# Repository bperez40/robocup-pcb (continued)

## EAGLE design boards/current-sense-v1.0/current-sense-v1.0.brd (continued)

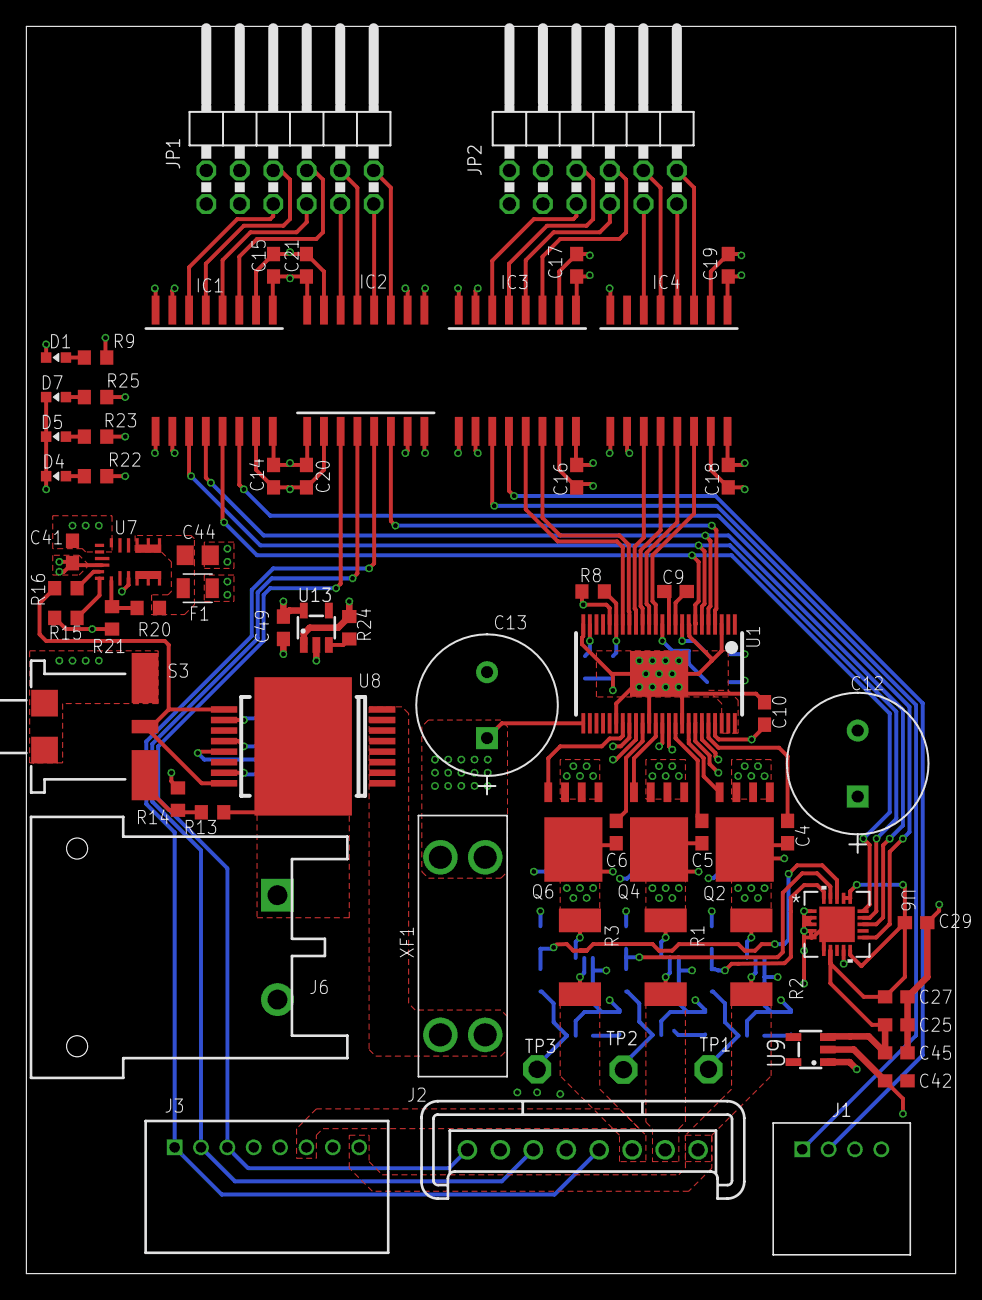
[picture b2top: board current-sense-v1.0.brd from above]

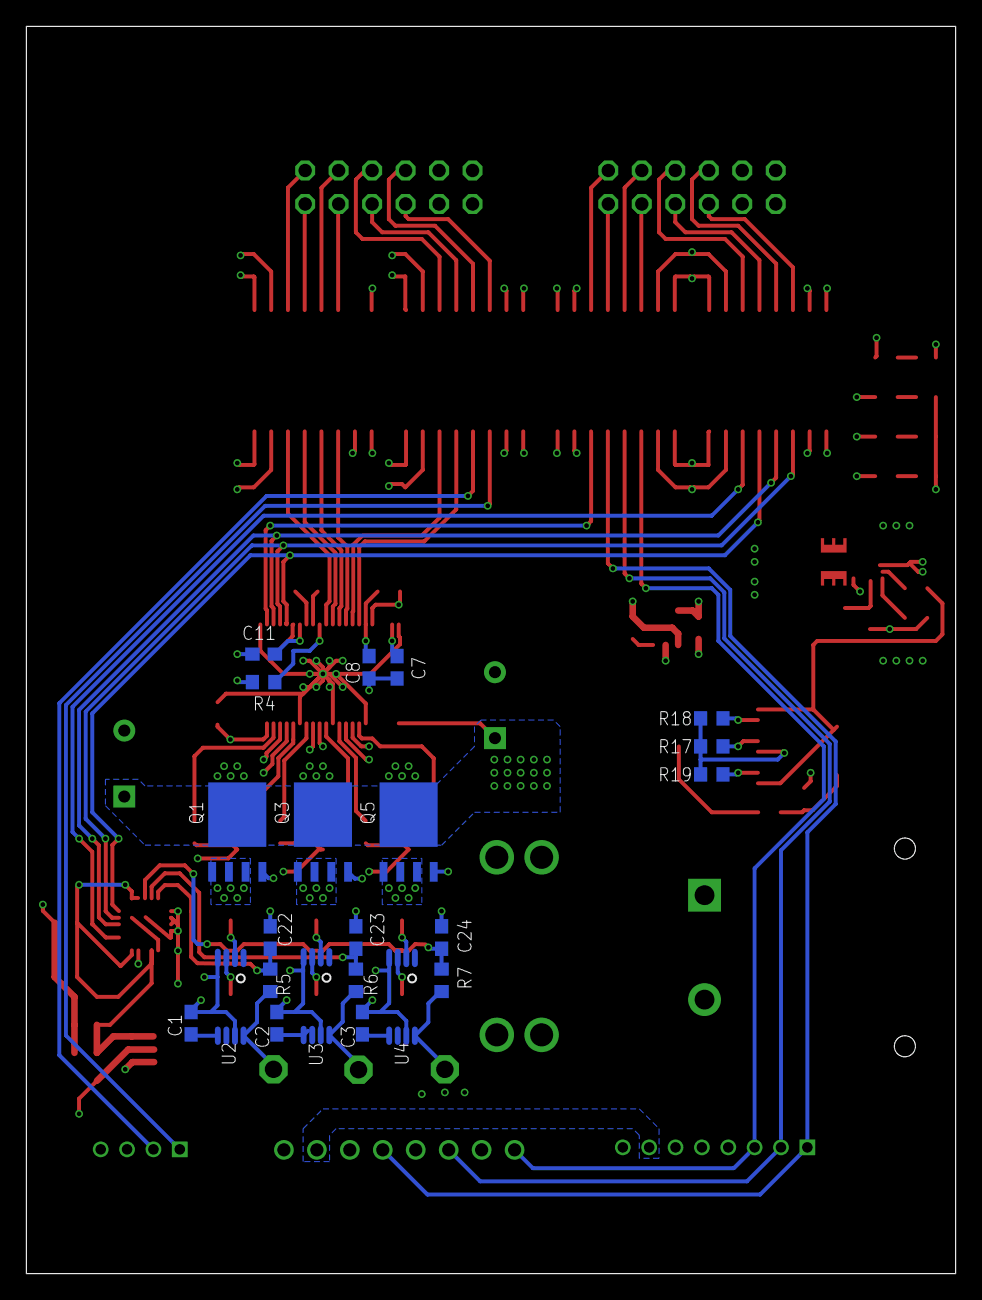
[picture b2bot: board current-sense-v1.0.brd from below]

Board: 4 copper layers, 70.5 x 94.6 mm, 89 parts (22 on the bottom side), 82 nets.

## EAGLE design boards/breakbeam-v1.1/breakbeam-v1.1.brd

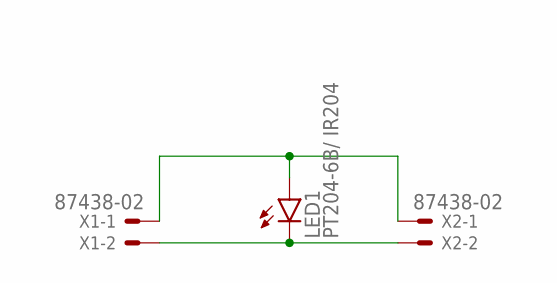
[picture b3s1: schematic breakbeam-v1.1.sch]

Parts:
LED1: PT204-6B/ IR204; LED3MM
X1, X2: 87438-02

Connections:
ANODE: LED1.A, X1.1, X2.1
CATHODE: LED1.K (C), X1.2, X2.2

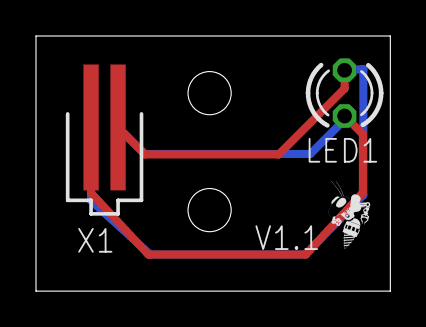
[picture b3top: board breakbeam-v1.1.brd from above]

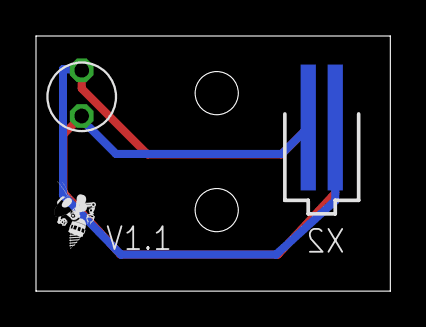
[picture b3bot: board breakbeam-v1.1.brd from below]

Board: 2 copper layers, 19.7 x 14.2 mm, 5 parts (2 on the bottom side), 2 nets.

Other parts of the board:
U$1, U$4: ROBOBUZZ_0.2X

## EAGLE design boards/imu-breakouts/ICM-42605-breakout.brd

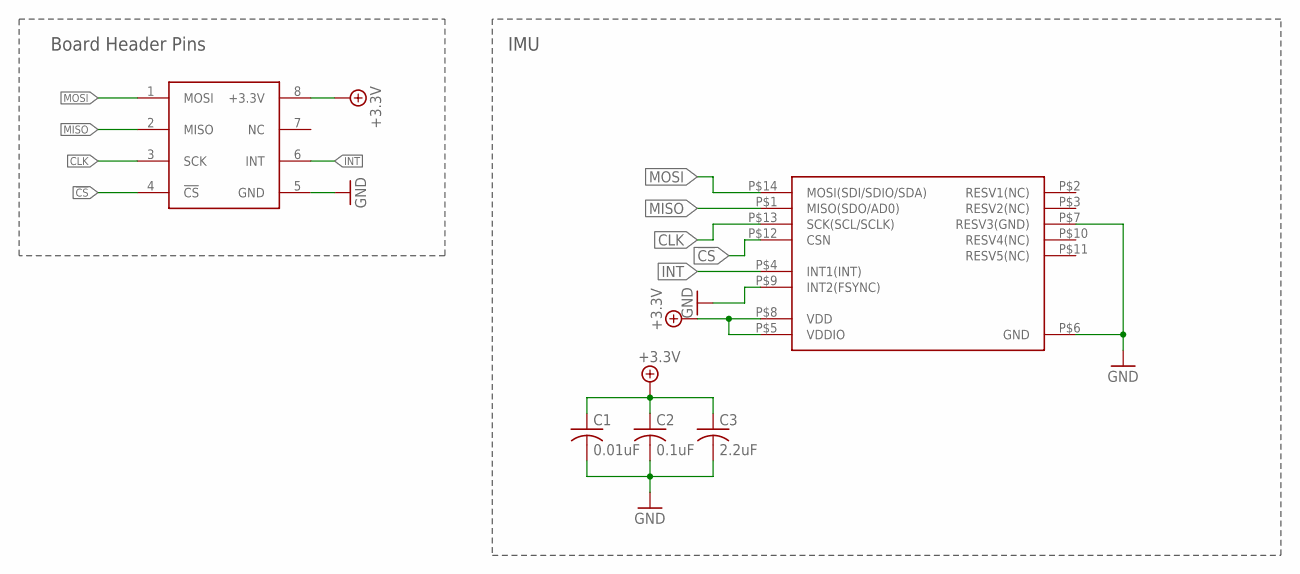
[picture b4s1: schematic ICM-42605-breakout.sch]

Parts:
C1: 0.01uF; C0603
C2: 0.1uF; C0603
C3: 2.2uF; C0603
KIT1: IMUIMU-KIT; IMU-KIT
U3: ICM-42605; ICM-442605-2530091

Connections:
!CS!: KIT1.4 (!CS!), U3.P$12 (CSN)
+3.3V: C1.1, C2.1, C3.1, KIT1.8 (+3.3V), U3.P$5 (VDDIO), U3.P$8 (VDD)
CLK: KIT1.3 (SCK), U3.P$13 (SCK(SCL/SCLK))
GND: C1.2, C2.2, C3.2, KIT1.5 (GND), U3.P$6 (GND), U3.P$7 (RESV3(GND)), U3.P$9 (INT2(FSYNC))
INT: KIT1.6 (INT), U3.P$4 (INT1(INT))
MISO: KIT1.2 (MISO), U3.P$1 (MISO(SDO/AD0))
MOSI: KIT1.1 (MOSI), U3.P$14 (MOSI(SDI/SDIO/SDA))

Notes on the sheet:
IMU
Board Header Pins

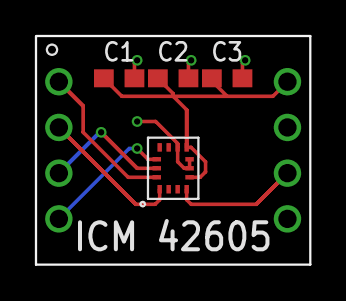
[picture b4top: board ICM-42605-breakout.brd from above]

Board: 2 copper layers, 15.2 x 12.7 mm, 5 parts (0 on the bottom side), 7 nets.

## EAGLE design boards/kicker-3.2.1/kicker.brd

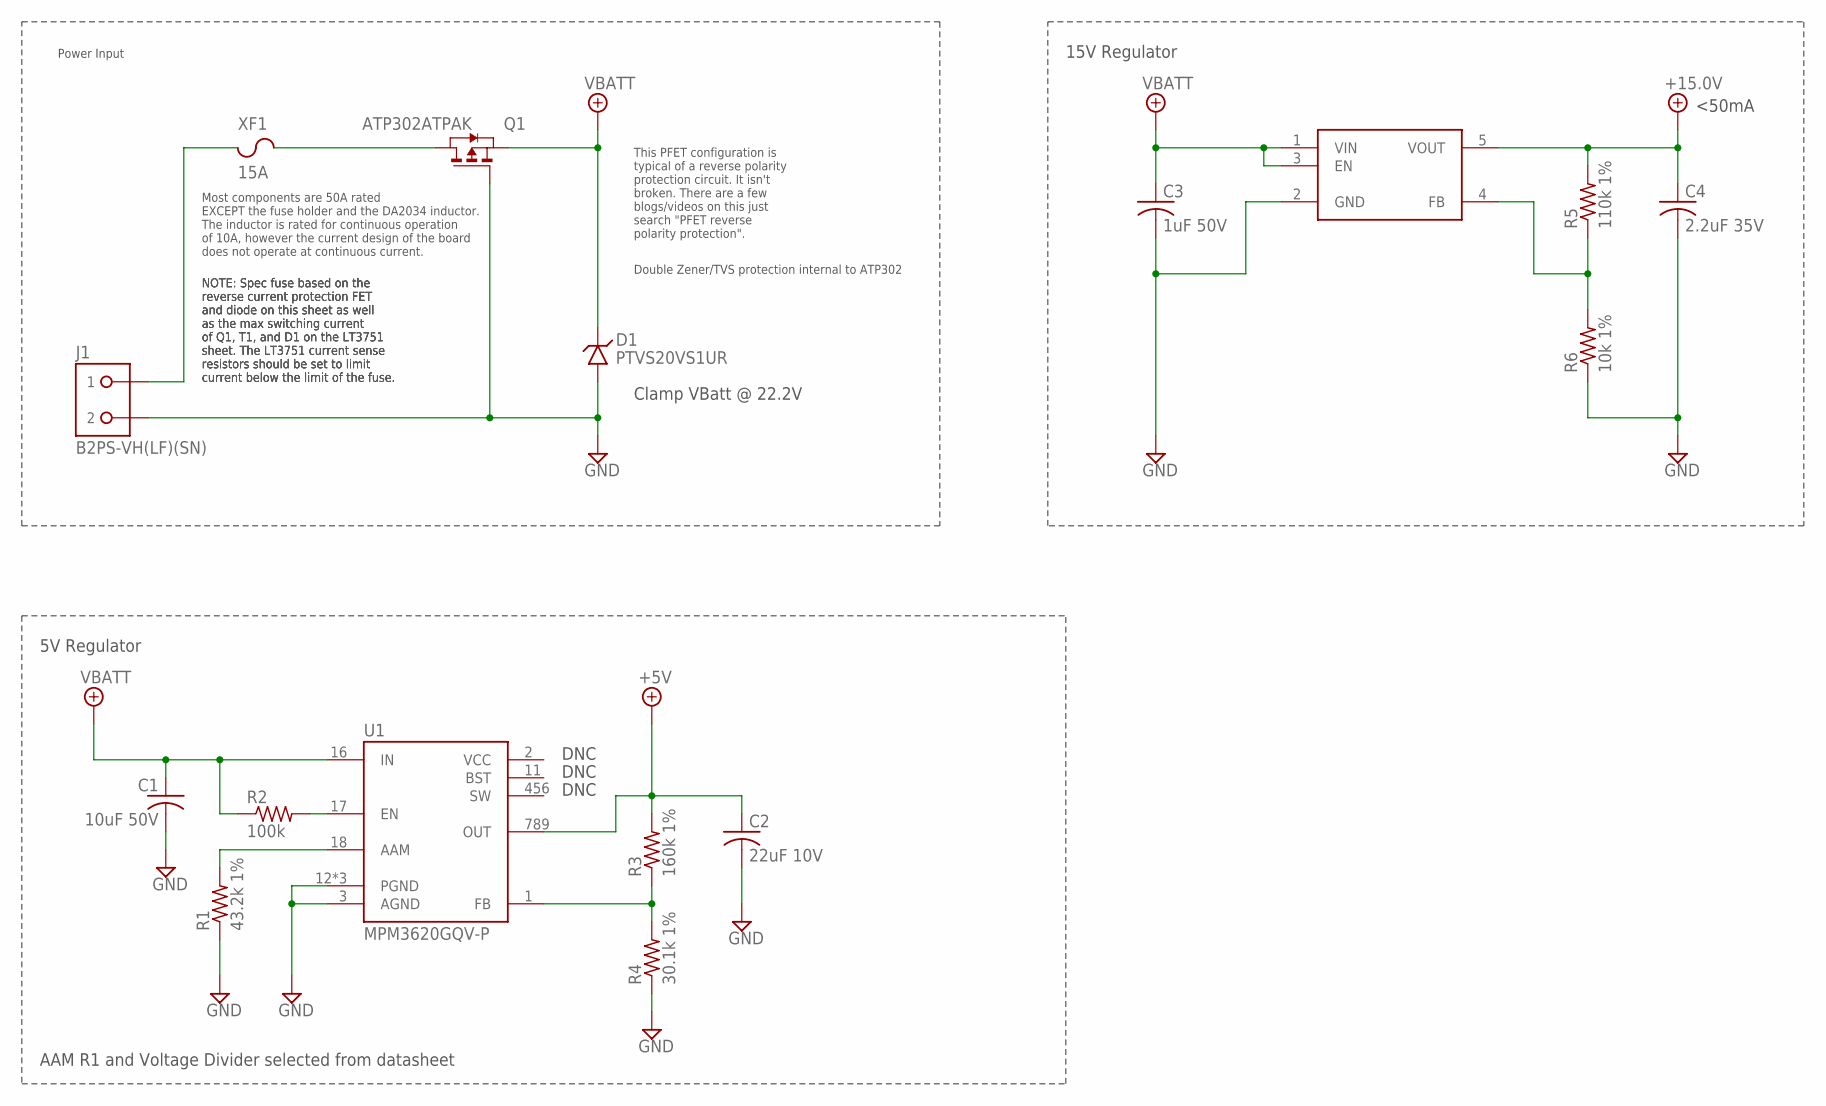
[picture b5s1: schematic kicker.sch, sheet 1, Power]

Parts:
C1: 10uF 50V; C1206
C2: 22uF 10V; C0603
C3: 1uF 50V; C0603
C4: 2.2uF 35V; C0603
D1: PTVS20VS1UR; SOD123-W
J1: B2PS-VH(LF)(SN); B2PS-CENTERED
Q1: ATP302ATPAK; TO460P950X150-3
R1: 43.2k 1%; R0603
R2: 100k; R0603
R3: 160k 1%; R0603
R4: 30.1k 1%; R0603
R5: 110k 1%; R0603
R6: 10k 1%; R0603
U1: MPM3620GQV-P
U2: 15V; SOT95P280X145-5
XF1: 15A; 3557-2

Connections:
+5V: C2.1, R3.2, U1.789 (OUT); also elsewhere on the board
+15.0V: C4.1, R5.2, U2.5 (VOUT); also elsewhere on the board
FB: R3.1, R4.2, U1.1 (FB)
GND: C1.2, C2.2, C3.2, C4.2, D1.A, J1.2, Q1.1 (G), R1.1, R4.1, R6.1, U1.3 (AGND), U1.12 (PGND), U1.13 (PGND), U1.14 (PGND), U2.2 (GND); also elsewhere on the board
unnamed: Q1.3 (D), XF1.3 (2), XF1.4 (2)
unnamed: R5.1, R6.2, U2.4 (FB)
unnamed: J1.1, XF1.1, XF1.2 (1)
REG_AAM: R1.2, U1.18 (AAM)
REG_EN: R2.2, U1.17 (EN)
VBATT: C1.1, C3.1, D1.C, Q1.2 (S), R2.1, U1.16 (IN), U2.1 (VIN), U2.3 (EN); also elsewhere on the board

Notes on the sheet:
Power Input
5V Regulator
NOTE: Spec fuse based on the reverse current protection FET and diode on this sheet as well as the max switching current of Q1, T1, and D1 on the LT3751 sheet. The LT3751 current sense resistors should be set to limit current below the limit of the fuse.
15V Regulator
This PFET configuration is typical of a reverse polarity protection circuit. It isn't broken. There are a few blogs/videos on this just search "PFET reverse polarity protection".
DNC
Clamp VBatt @ 22.2V
<50mA
AAM R1 and Voltage Divider selected from datasheet
Most components are 50A rated EXCEPT the fuse holder and the DA2034 inductor. The inductor is rated for continuous operation of 10A, however the current design of the board does not operate at continuous current.
Double Zener/TVS protection internal to ATP302

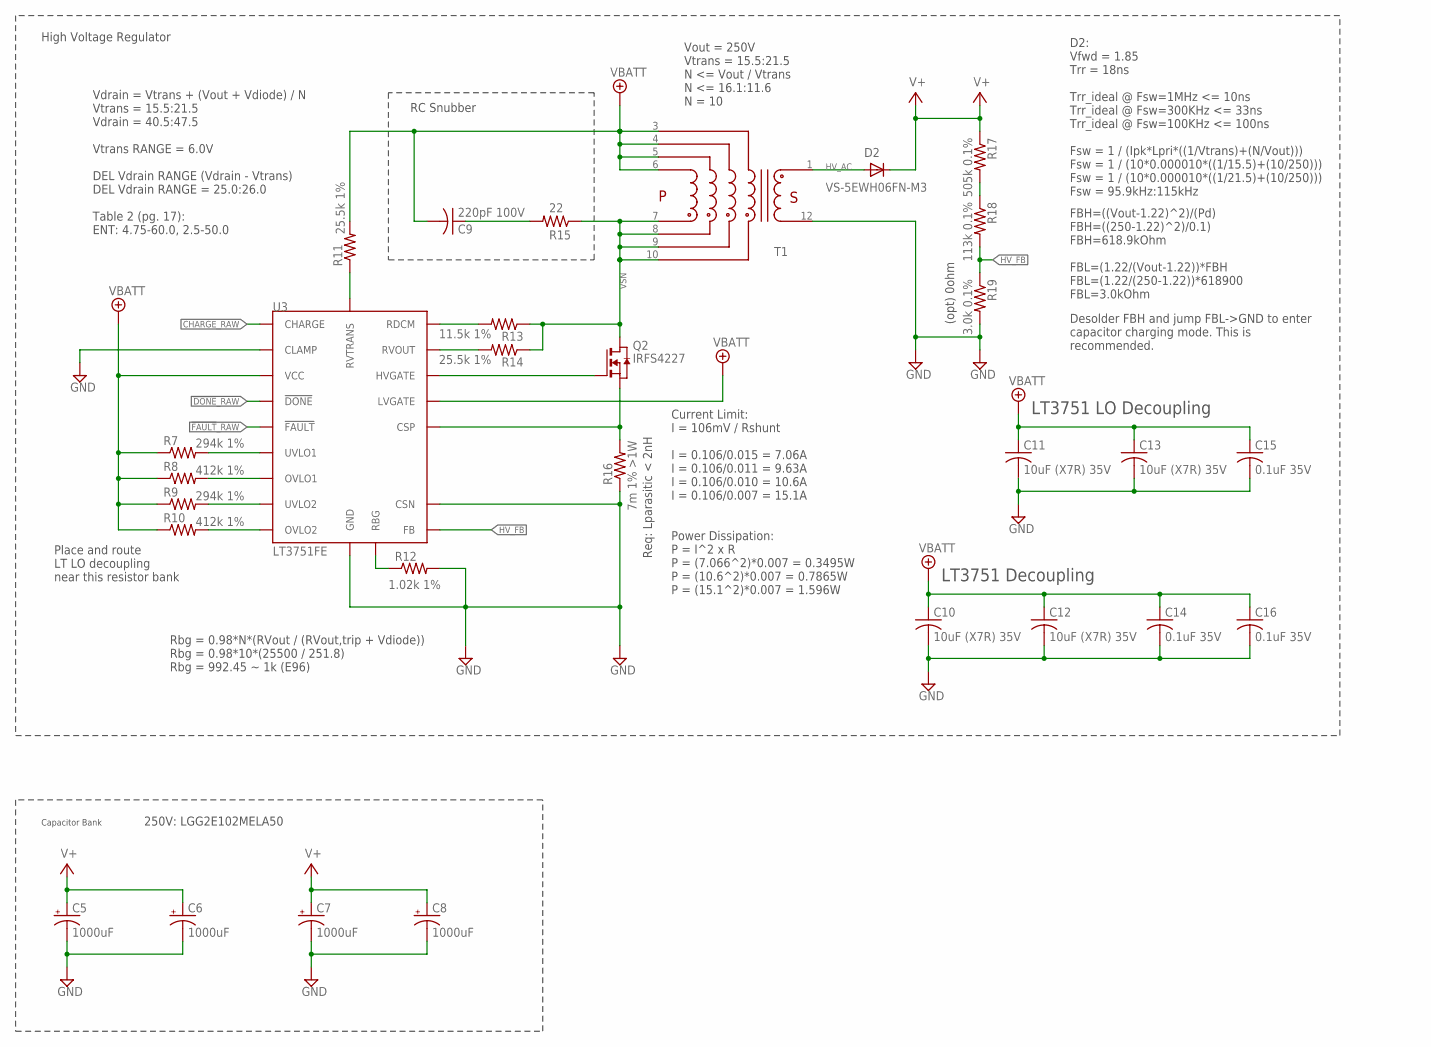
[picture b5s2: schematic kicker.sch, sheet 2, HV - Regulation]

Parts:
C5, C6, C7, C8: 1000uF; EB25D
C9: 220pF 100V; C0805
C10, C11, C12, C13: 10uF (X7R) 35V; C1210
C14, C15, C16: 0.1uF 35V; C0603
D2: VS-5EWH06FN-M3; TO460P990X239-3
Q2: IRFS4227; D2PAK
R7, R9: 294k 1%; R0603
R8, R10: 412k 1%; R0603
R11: 25.5k 1%; R0603
R12: 1.02k 1%; R0805
R13: 11.5k 1%; R0805
R14: 25.5k 1%; R0805
R15: 22; R0805
R16: 7m 1% >1W; R2512
R17: 505k 0.1%; R0603
R18: 113k 0.1%; R0603
R19: 3.0k 0.1%; R0603
T1: DA203X-ALDA2034; DA2034
U3: LT3751FE; TSSOP-20_EP

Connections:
!DONE!_RAW: U3.7 (!DONE); also elsewhere on the board
!FAULT!_RAW: U3.6 (!FAULT); also elsewhere on the board
CHARGE_RAW: U3.8 (CHARGE); also elsewhere on the board
CSP: Q2.3 (S), R16.2, U3.12 (CSP)
GND: C5.-, C6.-, C7.-, C8.-, C10.2, C11.2, C12.2, C13.2, C14.2, C15.2, C16.2, R12.2, R16.1, R19.2, T1.12, U3.9 (CLAMP), U3.11 (CSN), U3.PAD (GND); also elsewhere on the board
HVGATE: Q2.1 (G), U3.15 (HVGATE)
HV_AC: D2.2 (A), T1.1
HV_FB: R18.2, R19.1, U3.10 (FB)
unnamed: R12.1, U3.16 (RBG)
unnamed: R17.2, R18.1
unnamed: C9.1, R15.2
unnamed: R11.1, U3.1 (RVTRANS)
OVLO1: R8.2, U3.3 (OVLO1)
OVLO2: R10.2, U3.5 (OVLO2)
RDCM: R13.2, U3.20 (RDCM)
RVOUT: R14.2, U3.18 (RVOUT)
UVLO1: R7.2, U3.2 (UVLO1)
UVLO2: R9.2, U3.4 (UVLO2)
V+: C5.+, C6.+, C7.+, C8.+, D2.3 (C), R17.1; also elsewhere on the board
VBATT: C9.2, C10.1, C11.1, C12.1, C13.1, C14.1, C15.1, C16.1, R7.1, R8.1, R9.1, R10.1, R11.2, T1.3, T1.4, T1.5, T1.6, U3.13 (VCC), U3.14 (LVGATE); also elsewhere on the board
VSN: Q2.2 (D), R13.1, R14.1, R15.1, T1.7, T1.8, T1.9, T1.10

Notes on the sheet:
Capacitor Bank
High Voltage Regulator
250V: LGG2E102MELA50
RC Snubber
LT3751 LO Decoupling
LT3751 Decoupling
Place and route LT LO decoupling near this resistor bank
Desolder FBH and jump FBL->GND to enter capacitor charging mode. This is recommended.
(opt) 0ohm
Current Limit: I = 106mV / Rshunt I = 0.106/0.015 = 7.06A I = 0.106/0.011 = 9.63A I = 0.106/0.010 = 10.6A I = 0.106/0.007 = 15.1A Power Dissipation: P = I^2 x R P = (7.066^2)*0.007 = 0.3495W P = (10.6^2)*0.007 = 0.7865W P = (15.1^2)*0.007 = 1.596W
Vdrain = Vtrans + (Vout + Vdiode) / N Vtrans = 15.5:21.5 Vdrain = 40.5:47.5 Vtrans RANGE = 6.0V DEL Vdrain RANGE (Vdrain - Vtrans) DEL Vdrain RANGE = 25.0:26.0 Table 2 (pg. 17): ENT: 4.75-60.0, 2.5-50.0
Req: Lparasitic < 2nH
Rbg = 0.98*N*(RVout / (RVout,trip + Vdiode)) Rbg = 0.98*10*(25500 / 251.8) Rbg = 992.45 ~ 1k (E96)
Vout = 250V Vtrans = 15.5:21.5 N <= Vout / Vtrans N <= 16.1:11.6 N = 10
D2: Vfwd = 1.85 Trr = 18ns Trr_ideal @ Fsw=1MHz <= 10ns Trr_ideal @ Fsw=300KHz <= 33ns Trr_ideal @ Fsw=100KHz <= 100ns Fsw = 1 / (Ipk*Lpri*((1/Vtrans)+(N/Vout))) Fsw = 1 / (10*0.000010*((1/15.5)+(10/250))) Fsw = 1 / (10*0.000010*((1/21.5)+(10/250))) Fsw = 95.9kHz:115kHz
FBH=((Vout-1.22)^2)/(Pd) FBH=((250-1.22)^2)/0.1) FBH=618.9kOhm FBL=(1.22/(Vout-1.22))*FBH FBL=(1.22/(250-1.22))*618900 FBL=3.0kOhm

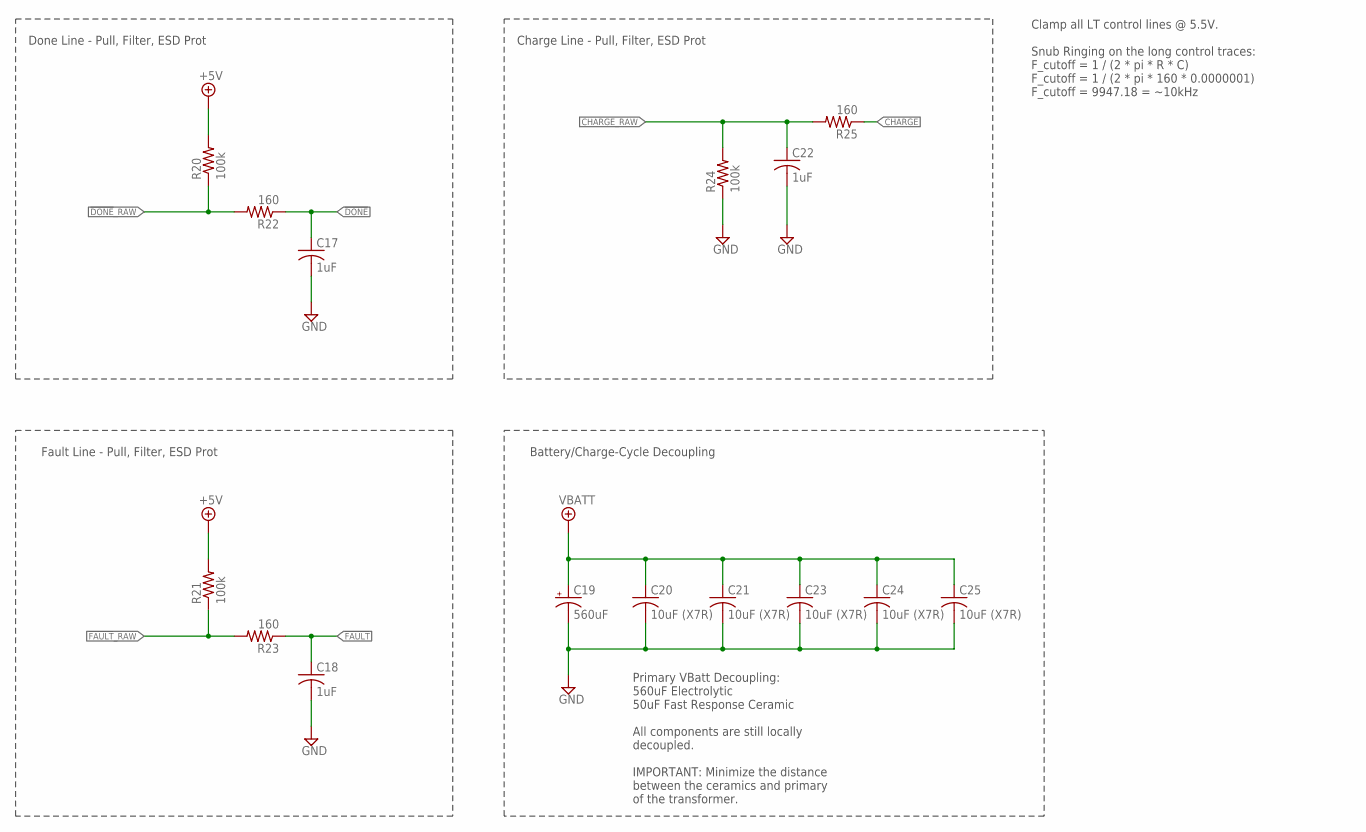
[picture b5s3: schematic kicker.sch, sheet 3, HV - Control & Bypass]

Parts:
C17, C18, C22: 1uF; C0603
C19: 560uF; E7,5-18
C20, C21, C23, C24, C25: 10uF (X7R); C1210
R20, R21, R24: 100k; R0603
R22, R23, R25: 160; R0603

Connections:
!DONE!: C17.1, R22.1; also elsewhere on the board
!DONE!_RAW: R20.1, R22.2; also elsewhere on the board
!FAULT!: C18.1, R23.1; also elsewhere on the board
!FAULT!_RAW: R21.1, R23.2; also elsewhere on the board
+5V: R20.2, R21.2; also elsewhere on the board
CHARGE: R25.1; also elsewhere on the board
CHARGE_RAW: C22.1, R24.2, R25.2; also elsewhere on the board
GND: C17.2, C18.2, C19.-, C20.2, C21.2, C22.2, C23.2, C24.2, C25.2, R24.1; also elsewhere on the board
VBATT: C19.+, C20.1, C21.1, C23.1, C24.1, C25.1; also elsewhere on the board

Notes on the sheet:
Done Line - Pull, Filter, ESD Prot
Fault Line - Pull, Filter, ESD Prot
Charge Line - Pull, Filter, ESD Prot
Battery/Charge-Cycle Decoupling
Clamp all LT control lines @ 5.5V. Snub Ringing on the long control traces: F_cutoff = 1 / (2 * pi * R * C) F_cutoff = 1 / (2 * pi * 160 * 0.0000001) F_cutoff = 9947.18 = ~10kHz
Primary VBatt Decoupling: 560uF Electrolytic 50uF Fast Response Ceramic All components are still locally decoupled. IMPORTANT: Minimize the distance between the ceramics and primary of the transformer.

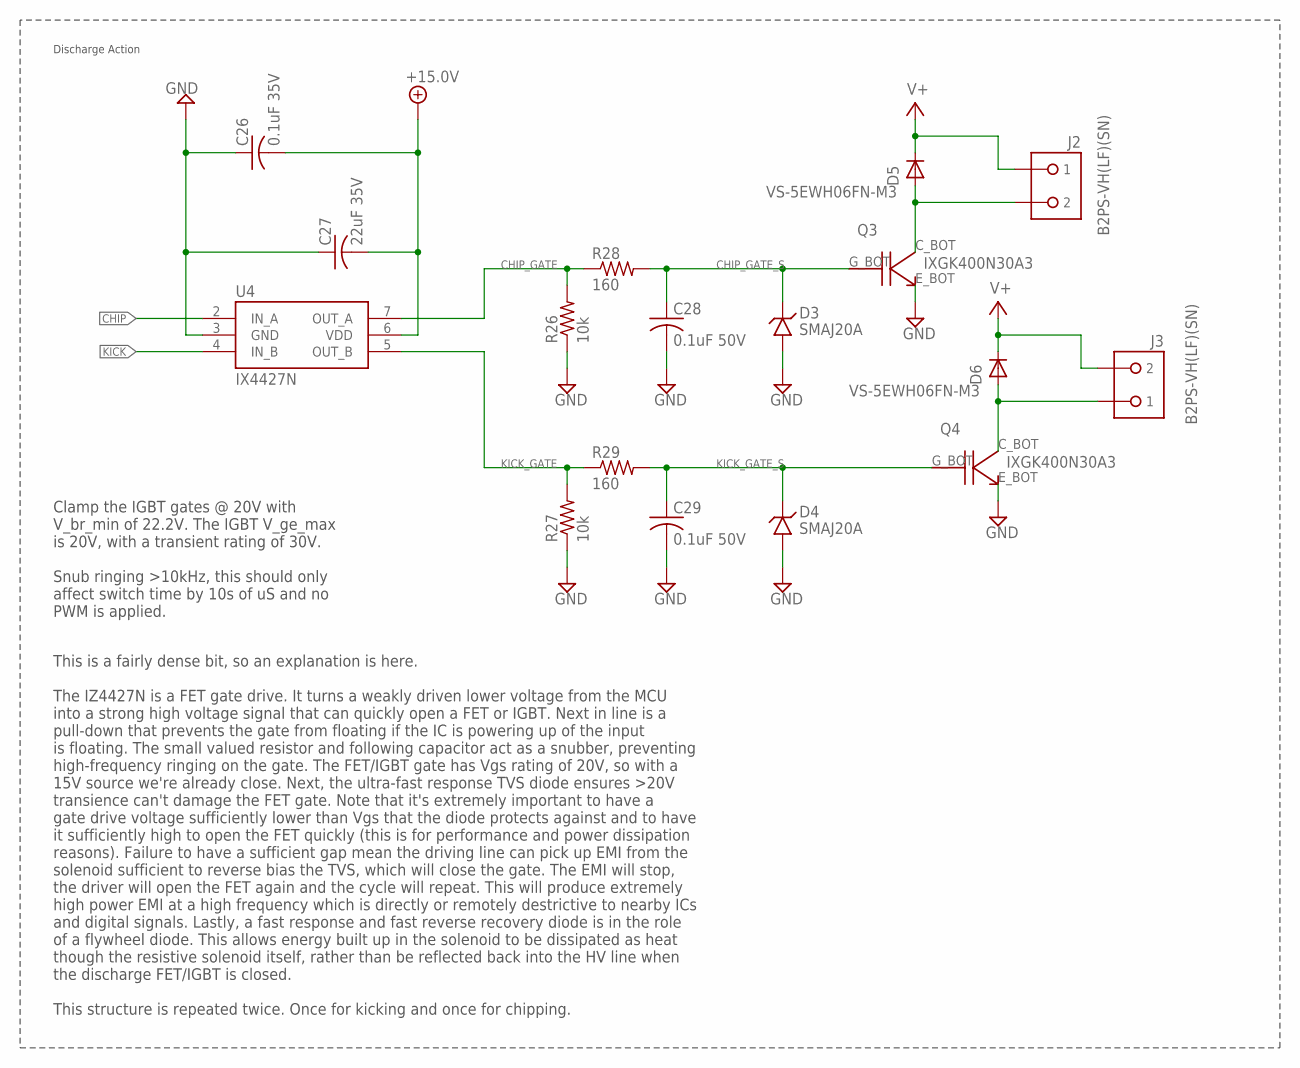
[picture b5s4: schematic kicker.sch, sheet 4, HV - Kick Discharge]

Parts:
C26: 0.1uF 35V; C0603
C27: 22uF 35V; C0603
C28, C29: 0.1uF 50V; C0603
D3, D4: SMAJ20A; RESM5226X262
D5, D6: VS-5EWH06FN-M3; TO460P990X239-3
J2, J3: B2PS-VH(LF)(SN); B2PS-CENTERED
Q3, Q4: IXGK400N30A3; TO264
R26, R27: 10k; R0603
R28, R29: 160; R1206
U4: IX4427N; SOIC-8

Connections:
+15.0V: C26.2, C27.2, U4.6 (VDD); also elsewhere on the board
CHIP: U4.2 (IN_A); also elsewhere on the board
CHIPPER: D5.2 (A), J2.2, Q3.C_BOT (C)
CHIP_GATE: R26.2, R28.1, U4.7 (OUT_A)
CHIP_GATE_S: C28.1, D3.2 (C), Q3.G_BOT (G), R28.2
GND: C26.1, C27.1, C28.2, C29.2, D3.1 (A), D4.1 (A), Q3.E_BOT (E), Q4.E_BOT (E), R26.1, R27.1, U4.3 (GND); also elsewhere on the board
KICK: U4.4 (IN_B); also elsewhere on the board
KICKER: D6.2 (A), J3.1, Q4.C_BOT (C)
KICK_GATE: R27.2, R29.1, U4.5 (OUT_B)
KICK_GATE_S: C29.1, D4.2 (C), Q4.G_BOT (G), R29.2
V+: D5.3 (C), D6.3 (C), J2.1, J3.2; also elsewhere on the board

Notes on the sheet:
Discharge Action
Clamp the IGBT gates @ 20V with V_br_min of 22.2V. The IGBT V_ge_max is 20V, with a transient rating of 30V. Snub ringing >10kHz, this should only affect switch time by 10s of uS and no PWM is applied.
This is a fairly dense bit, so an explanation is here. The IZ4427N is a FET gate drive. It turns a weakly driven lower voltage from the MCU into a strong high voltage signal that can quickly open a FET or IGBT. Next in line is a pull-down that prevents the gate from floating if the IC is powering u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

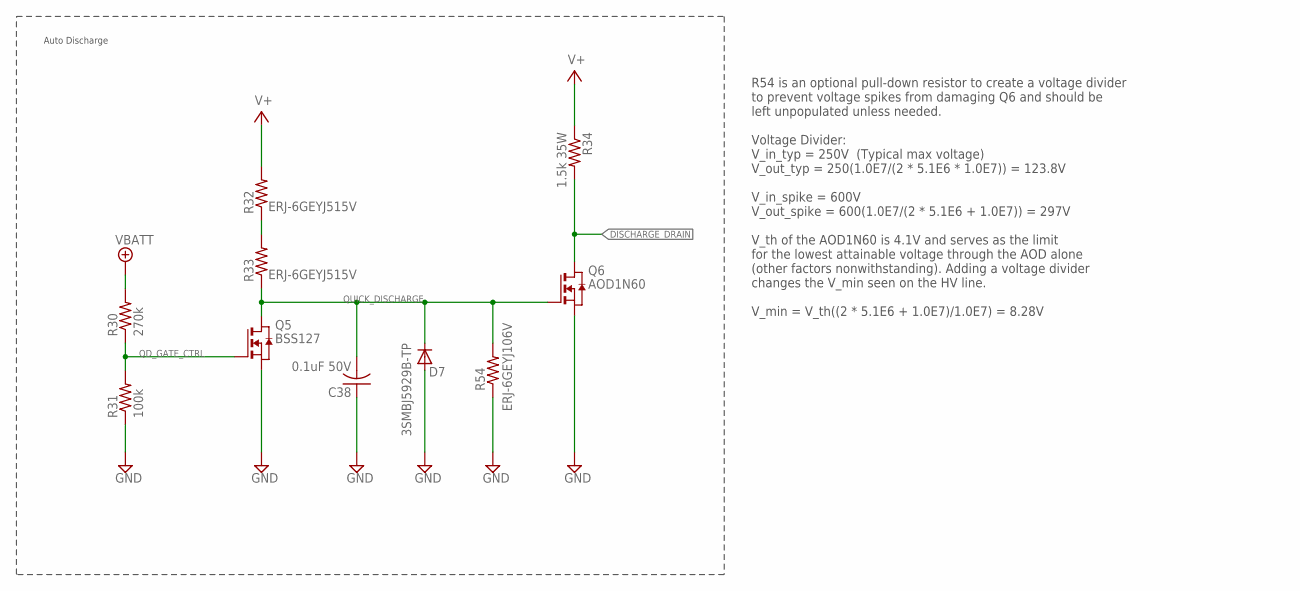
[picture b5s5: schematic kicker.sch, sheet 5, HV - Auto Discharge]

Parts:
C38: 0.1uF 50V; C0603
D7: 3SMBJ5929B-TP; DO214AA
Q5: BSS127; SOT-23-3
Q6: AOD1N60; DPAK
R30: 270k; R0603
R31: 100k; R0603
R32: ERJ-6GEYJ515V; R0603
R33: ERJ-6GEYJ515V; R0805
R34: 1.5k 35W; TO508P1539X450-3
R54: ERJ-6GEYJ106V; R0603

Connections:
DISCHARGE_DRAIN: Q6.FIN (D), R34.2 (PIN2); also elsewhere on the board
GND: C38.1, D7.A, Q5.2 (S), Q6.3 (S), R31.1, R54.1; also elsewhere on the board
QD_GATE_CTRL: Q5.1 (G), R30.1, R31.2
QD_PU_BR: R32.1, R33.2
QUICK_DISCHARGE: C38.2, D7.C, Q5.3 (D), Q6.1 (G), R33.1, R54.2
V+: R32.2, R34.1 (PIN1); also elsewhere on the board
VBATT: R30.2; also elsewhere on the board

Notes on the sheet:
Auto Discharge
R54 is an optional pull-down resistor to create a voltage divider to prevent voltage spikes from damaging Q6 and should be left unpopulated unless needed. Voltage Divider: V_in_typ = 250V (Typical max voltage) V_out_typ = 250(1.0E7/(2 * 5.1E6 * 1.0E7)) = 123.8V V_in_spike = 600V V_out_spike = 600(1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

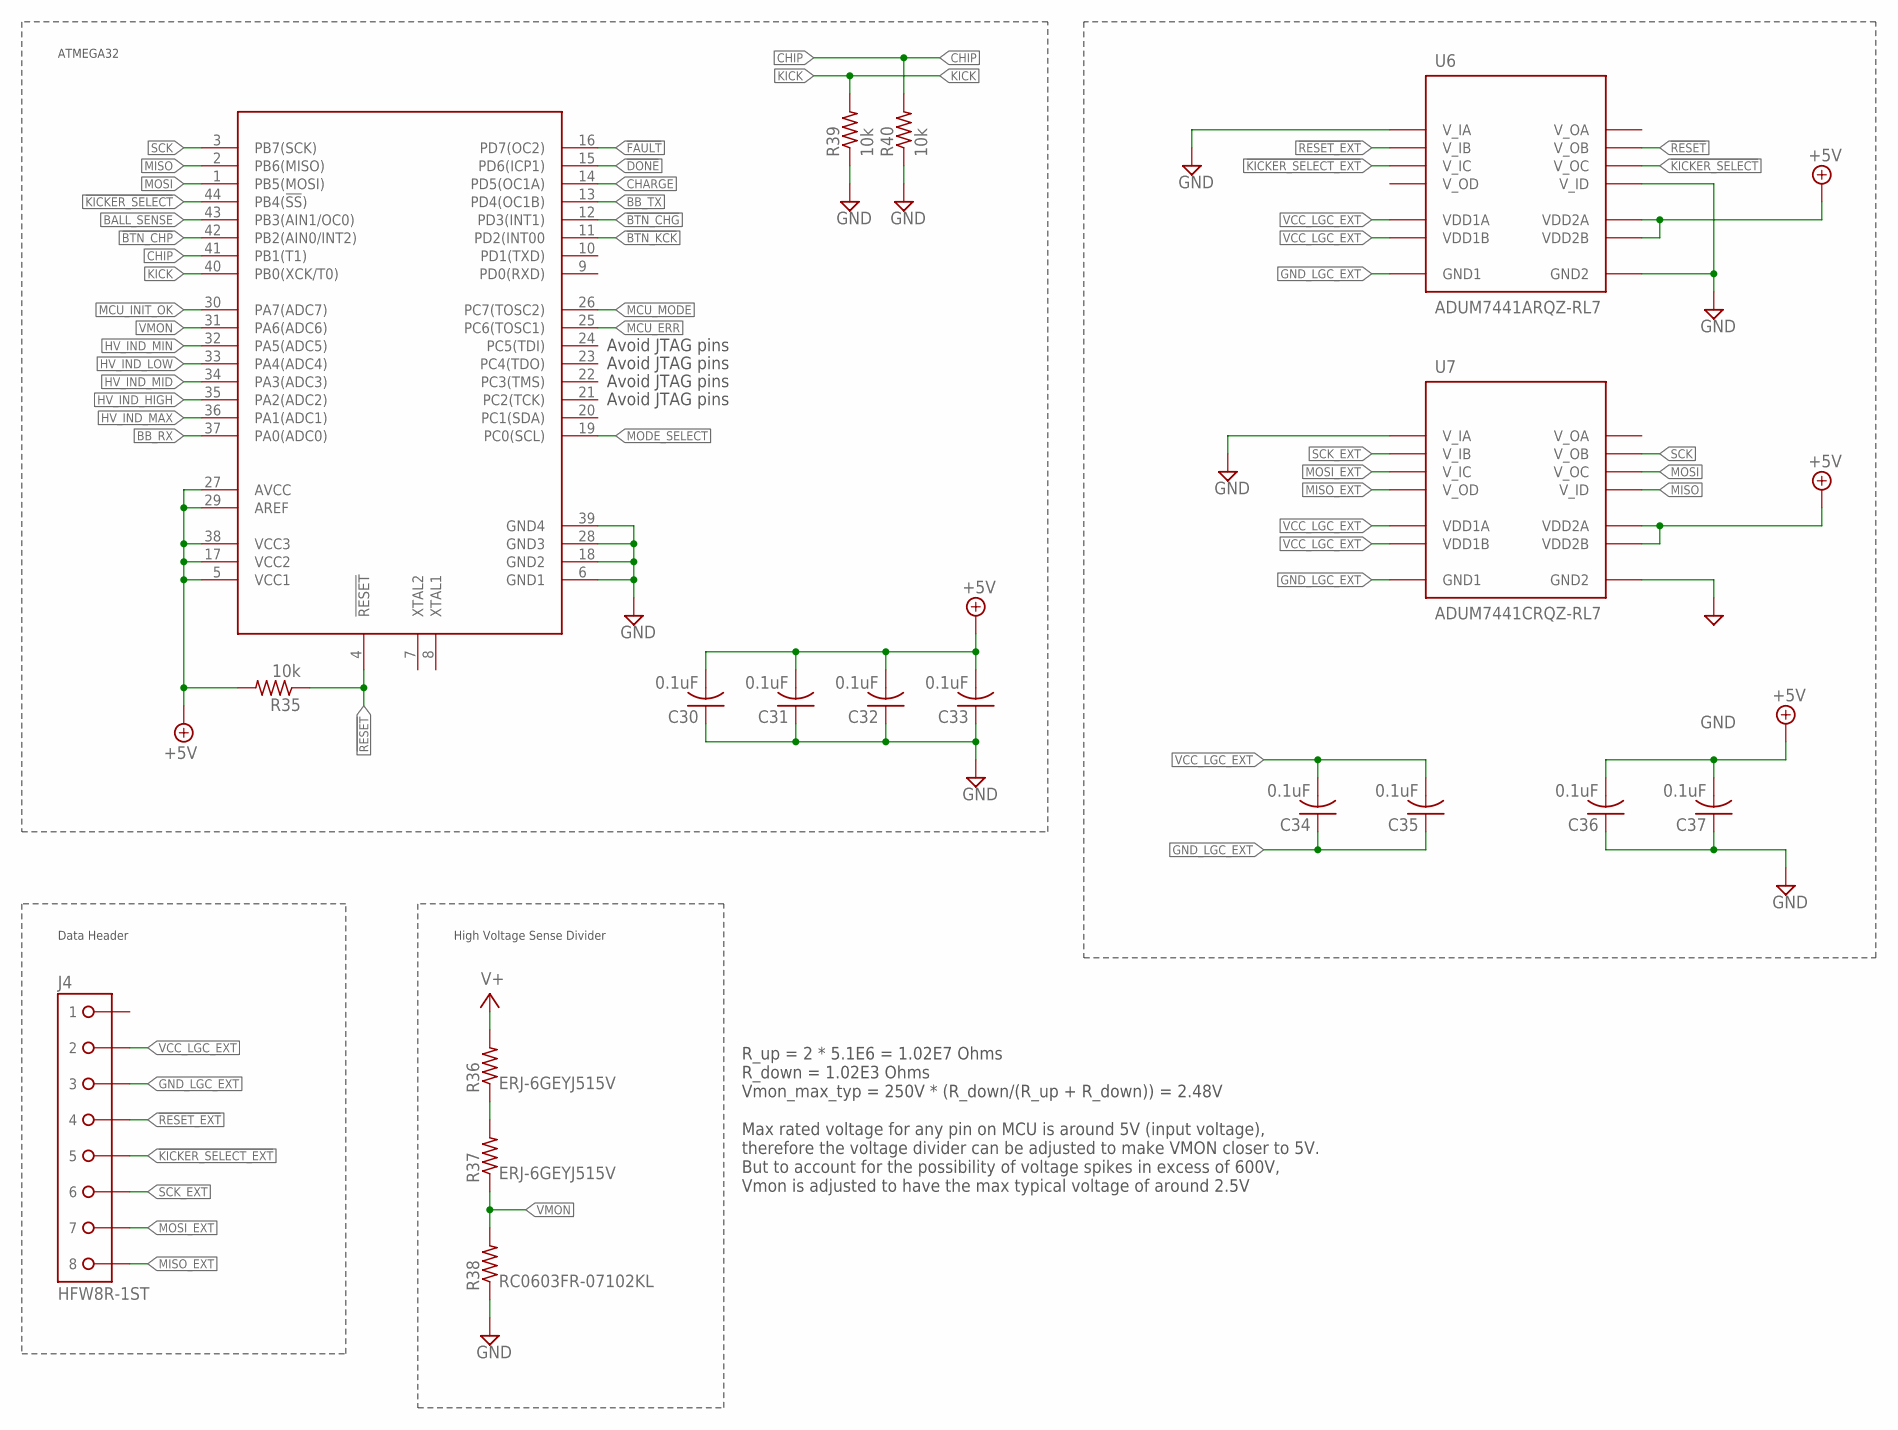
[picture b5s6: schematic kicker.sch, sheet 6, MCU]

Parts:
C30, C31, C32, C33, C34, C35, C36, C37: 0.1uF; C0603
J4: HFW8R-1ST
R35, R39, R40: 10k; R0603
R36, R37: ERJ-6GEYJ515V; R0603
R38: RC0603FR-07102KL; R0603
U5: AT32ATQFP44; QFP80P1200X1200X120-44
U6: ADUM7441ARQZ-RL7; SOP63P574X165-16
U7: ADUM7441CRQZ-RL7; SOP63P574X165-16

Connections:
!BTN_CHG: U5.12 (PD3(INT1)); also elsewhere on the board
!BTN_CHP: U5.42 (PB2(AIN0/INT2)); also elsewhere on the board
!BTN_KCK: U5.11 (PD2(INT00); also elsewhere on the board
!DONE!: U5.15 (PD6(ICP1)); also elsewhere on the board
!FAULT!: U5.16 (PD7(OC2)); also elsewhere on the board
!KICKER_SELECT: U5.44 (PB4(!SS!)), U6.12 (V_OC)
!KICKER_SELECT_EXT: J4.5, U6.5 (V_IC)
!RESET: R35.1, U5.4 (!RESET!), U6.13 (V_OB)
!RESET_EXT: J4.4, U6.4 (V_IB)
+5V: C30.2, C31.2, C32.2, C33.2, C36.2, C37.2, R35.2, U5.5 (VCC1), U5.17 (VCC2), U5.27 (AVCC), U5.29 (AREF), U5.38 (VCC3), U6.10 (VDD2B), U6.16 (VDD2A), U7.10 (VDD2B), U7.16 (VDD2A); also elsewhere on the board
BALL_SENSE: U5.43 (PB3(AIN1/OC0)); also elsewhere on the board
BB_RX: U5.37 (PA0(ADC0)); also elsewhere on the board
BB_TX: U5.13 (PD4(OC1B)); also elsewhere on the board
CHARGE: U5.14 (PD5(OC1A)); also elsewhere on the board
CHIP: R40.2, U5.41 (PB1(T1)); also elsewhere on the board
GND: C30.1, C31.1, C32.1, C33.1, C36.1, C37.1, R38.1, R39.1, R40.1, U5.6 (GND1), U5.18 (GND2), U5.28 (GND3), U5.39 (GND4), U6.3 (V_IA), U6.9 (GND2), U6.11 (V_ID), U6.15 (GND2), U7.3 (V_IA), U7.9 (GND2), U7.15 (GND2); also elsewhere on the board
GND_LGC_EXT: C34.1, C35.1, J4.3, U6.2 (GND1), U6.8 (GND1), U7.2 (GND1), U7.8 (GND1)
HV_IND_HIGH: U5.35 (PA2(ADC2)); also elsewhere on the board
HV_IND_LOW: U5.33 (PA4(ADC4)); also elsewhere on the board
HV_IND_MAX: U5.36 (PA1(ADC1)); also elsewhere on the board
HV_IND_MID: U5.34 (PA3(ADC3)); also elsewhere on the board
HV_IND_MIN: U5.32 (PA5(ADC5)); also elsewhere on the board
HV_SENSE_DIV_BR: R36.1, R37.2
KICK: R39.2, U5.40 (PB0(XCK/T0)); also elsewhere on the board
MCU_ERR: U5.25 (PC6(TOSC1)); also elsewhere on the board
MCU_INIT_OK: U5.30 (PA7(ADC7)); also elsewhere on the board
MCU_MODE: U5.26 (PC7(TOSC2)); also elsewhere on the board
MISO: U5.2 (PB6(MISO)), U7.11 (V_ID)
MISO_EXT: J4.8, U7.6 (V_OD)
MODE_SELECT: U5.19 (PC0(SCL)); also elsewhere on the board
MOSI: U5.1 (PB5(MOSI)), U7.12 (V_OC)
MOSI_EXT: J4.7, U7.5 (V_IC)
SCK: U5.3 (PB7(SCK)), U7.13 (V_OB)
SCK_EXT: J4.6, U7.4 (V_IB)
V+: R36.2; also elsewhere on the board
VCC_LGC_EXT: C34.2, C35.2, J4.2, U6.1 (VDD1A), U6.7 (VDD1B), U7.1 (VDD1A), U7.7 (VDD1B)
VMON: R37.1, R38.2, U5.31 (PA6(ADC6))

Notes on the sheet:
ATMEGA32
Data Header
High Voltage Sense Divider
Avoid JTAG pins
R_up = 2 * 5.1E6 = 1.02E7 Ohms R_down = 1.02E3 Ohms Vmon_max_typ = 250V * (R_down/(R_up + R_down)) = 2.48V Max rated voltage for any pin on MCU is around 5V (input voltage), therefore the voltage divider can be adjusted to make VMON closer to 5V. But to account for the possibility of voltage spikes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

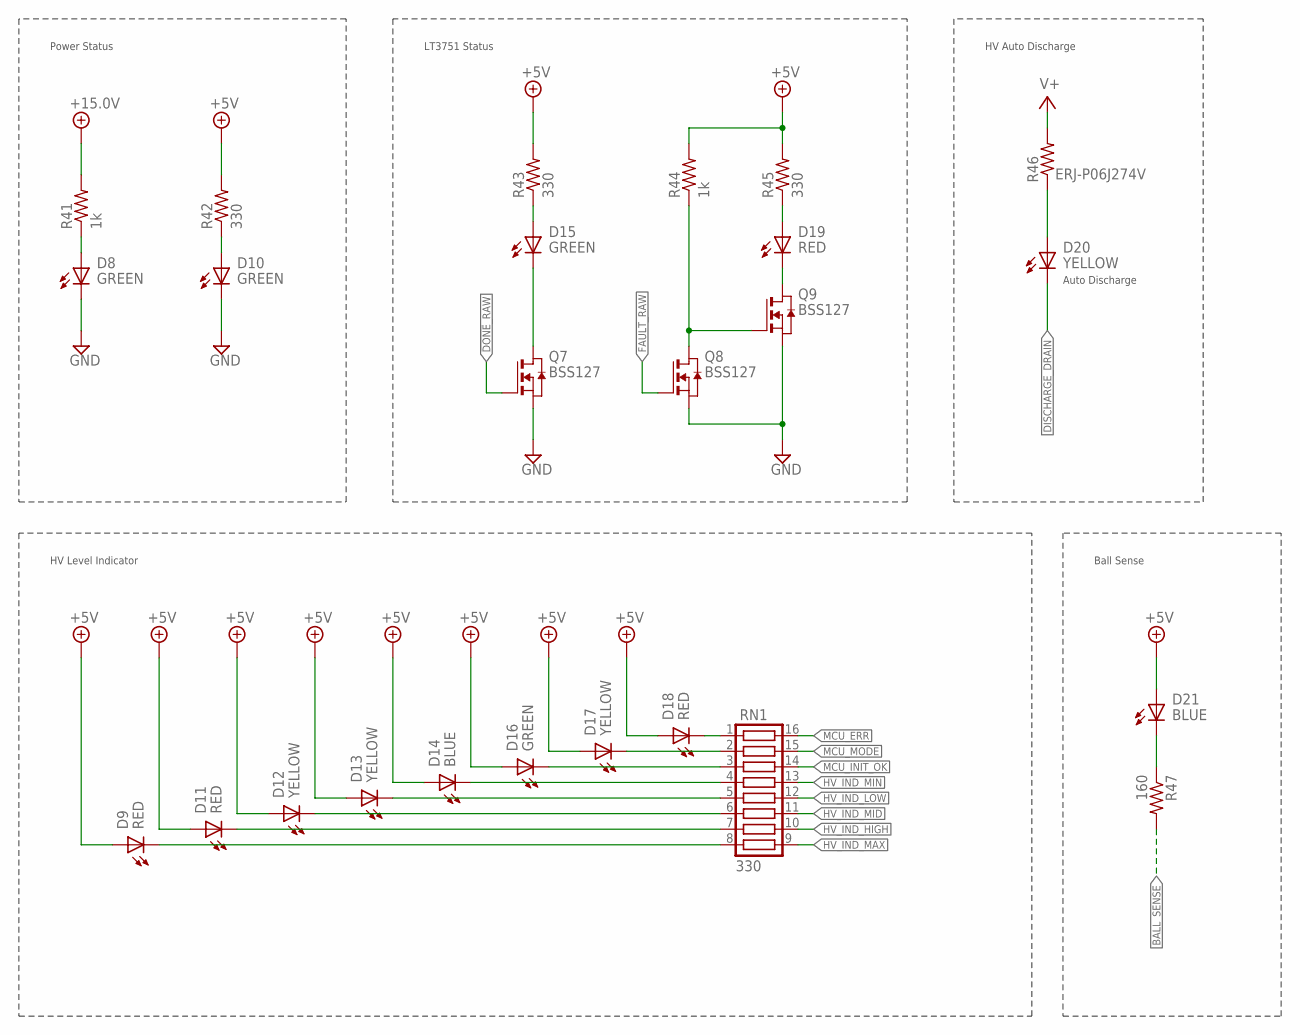
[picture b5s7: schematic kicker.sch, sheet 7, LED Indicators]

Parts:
D8, D10, D15, D16: GREEN; CHIP-LED0603
D9, D11, D18, D19: RED; CHIP-LED0603
D12, D13, D17, D20: YELLOW; CHIP-LED0603
D14, D21: BLUE; CHIP-LED0603
Q7, Q8, Q9: BSS127; SOT-23-3
R41, R44: 1k; R0603
R42, R43, R45: 330; R0603
R46: ERJ-P06J274V; R0805
R47: 160; R0603
RN1: 330; RA-8_2506

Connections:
15V_PWR_BR: D8.A, R41.1
!DONE!_RAW: Q7.1 (G); also elsewhere on the board
!FAULT!_RAW: Q8.1 (G); also elsewhere on the board
+5V: D9.A, D11.A, D12.A, D13.A, D14.A, D16.A, D17.A, D18.A, D21.A, R42.2, R43.2, R44.2, R45.2; also elsewhere on the board
+15.0V: R41.2; also elsewhere on the board
BALL_SENSE: R47.2; also elsewhere on the board
BALL_SENSE_CL: D21.C (K), R47.1
DISCHARGE_DRAIN: D20.C (K); also elsewhere on the board
FAULT_INV_BR: Q8.3 (D), Q9.1 (G), R44.1
GND: D8.C (K), D10.C (K), Q7.2 (S), Q8.2 (S), Q9.2 (S); also elsewhere on the board
HV_IND_HIGH: RN1.10; also elsewhere on the board
HV_IND_HIGH_CL: D11.C (K), RN1.7
HV_IND_LOW: RN1.12; also elsewhere on the board
HV_IND_LOW_CL: D13.C (K), RN1.5
HV_IND_MAX: RN1.9; also elsewhere on the board
HV_IND_MAX_CL: D9.C (K), RN1.8
HV_IND_MID: RN1.11; also elsewhere on the board
HV_IND_MID_CL: D12.C (K), RN1.6
HV_IND_MIN: RN1.13; also elsewhere on the board
HV_IND_MIN_CL: D14.C (K), RN1.4
MCU_ERR: RN1.16; also elsewhere on the board
MCU_ERR_CL: D18.C (K), RN1.1
MCU_INIT_OK: RN1.14; also elsewhere on the board
MCU_INIT_OK_CL: D16.C (K), RN1.3
MCU_MODE: RN1.15; also elsewhere on the board
MCU_MODE_CL: D17.C (K), RN1.2
unnamed: D15.A, R43.1
unnamed: D10.A, R42.1
unnamed: D19.A, R45.1
unnamed: D19.C (K), Q9.3 (D)
unnamed: D20.A, R46.1
unnamed: D15.C (K), Q7.3 (D)
V+: R46.2; also elsewhere on the board

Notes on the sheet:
Power Status
LT3751 Status
Auto Discharge
HV Auto Discharge
HV Level Indicator
Ball Sense
